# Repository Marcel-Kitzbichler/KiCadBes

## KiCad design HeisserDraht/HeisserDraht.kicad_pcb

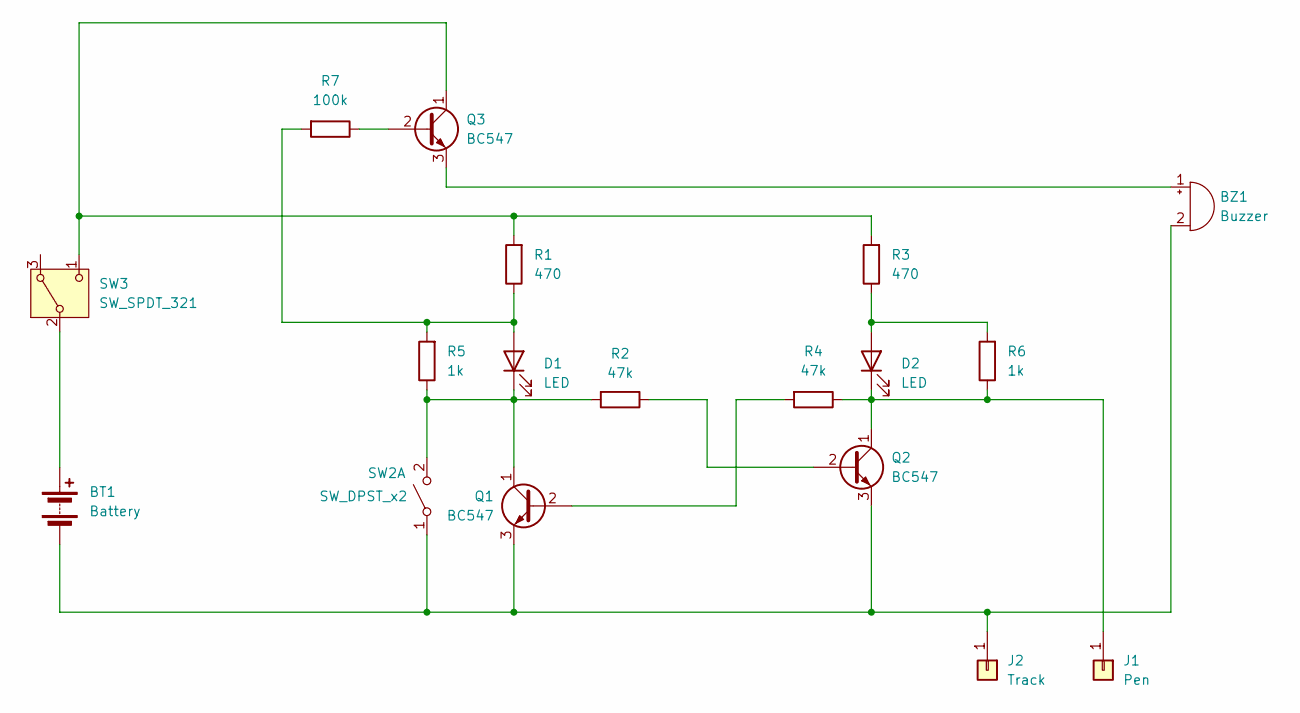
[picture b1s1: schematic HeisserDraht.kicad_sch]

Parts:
BT1: Battery; SolderWire-0.127sqmm_1x02_P3.7mm_D0.48mm_OD1mm_Relief2x
BZ1: Buzzer; BuzzerP_15,24
D1, D2: LED; LED_D5.0mm
J1: Pen; SolderWire-0.5sqmm_1x01_D0.9mm_OD2.3mm_Relief
J2: Track; SolderWire-1.5sqmm_1x01_D1.7mm_OD3.9mm
Q1, Q2, Q3: BC547; TO-92_Inline_Wide
R1, R3: 470; R_Axial_DIN0207_L6.3mm_D2.5mm_P10.16mm_Horizontal
R2, R4: 47k; R_Axial_DIN0207_L6.3mm_D2.5mm_P10.16mm_Horizontal
R5, R6: 1k; R_Axial_DIN0207_L6.3mm_D2.5mm_P10.16mm_Horizontal
R7: 100k; R_Axial_DIN0207_L6.3mm_D2.5mm_P10.16mm_Horizontal
SW2: SW_DPST_x2; SW_PUSH_6mm
SW3: SW_SPDT_321; SW_Slide-03_Wuerth-WS-SLTV_10x2.5x6.4_P2.54mm

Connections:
unnamed: BT1.1 (+), SW3.2 (B)
unnamed: BT1.2 (-), BZ1.2 (-), J2.1, Q1.3 (E), Q2.3 (E), SW2.1 (A)
unnamed: BZ1.1 (+), Q3.3 (E)
unnamed: D1.2 (A), R1.1, R5.2, R7.2
unnamed: D1.1 (K), Q1.1 (C), R2.2, R5.1, SW2.2 (B)
unnamed: D2.2 (A), R3.1, R6.2
unnamed: D2.1 (K), J1.1, Q2.1 (C), R4.1, R6.1
unnamed: Q1.2 (B), R4.2
unnamed: Q2.2 (B), R2.1
unnamed: Q3.2 (B), R7.1
unnamed: Q3.1 (C), R1.2, R3.2, SW3.1 (C)

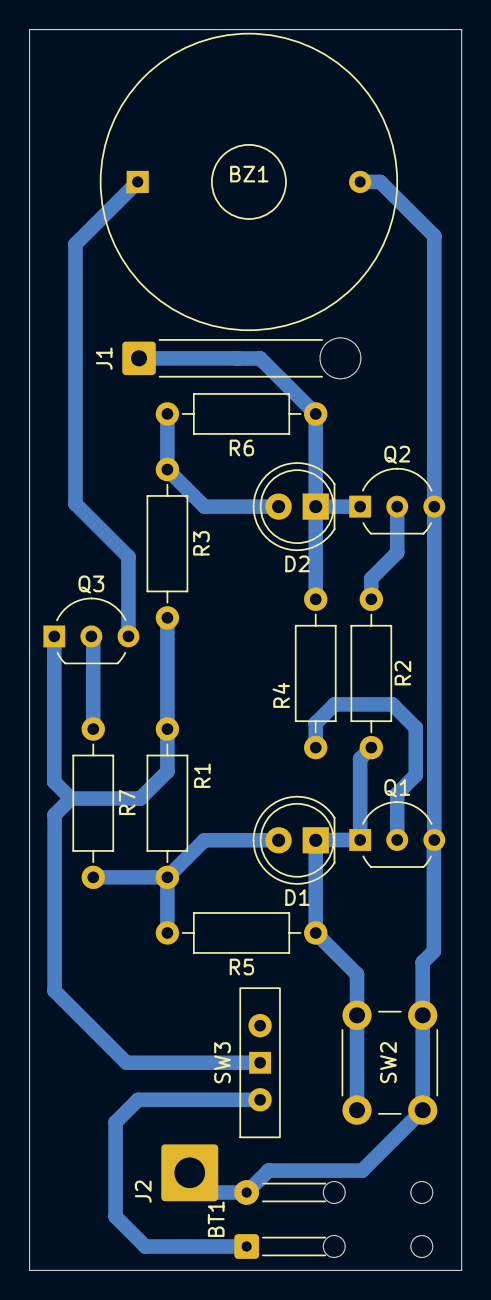
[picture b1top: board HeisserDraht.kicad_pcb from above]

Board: 2 copper layers, 29.6 x 85.0 mm, 18 parts (0 on the bottom side), 11 nets.

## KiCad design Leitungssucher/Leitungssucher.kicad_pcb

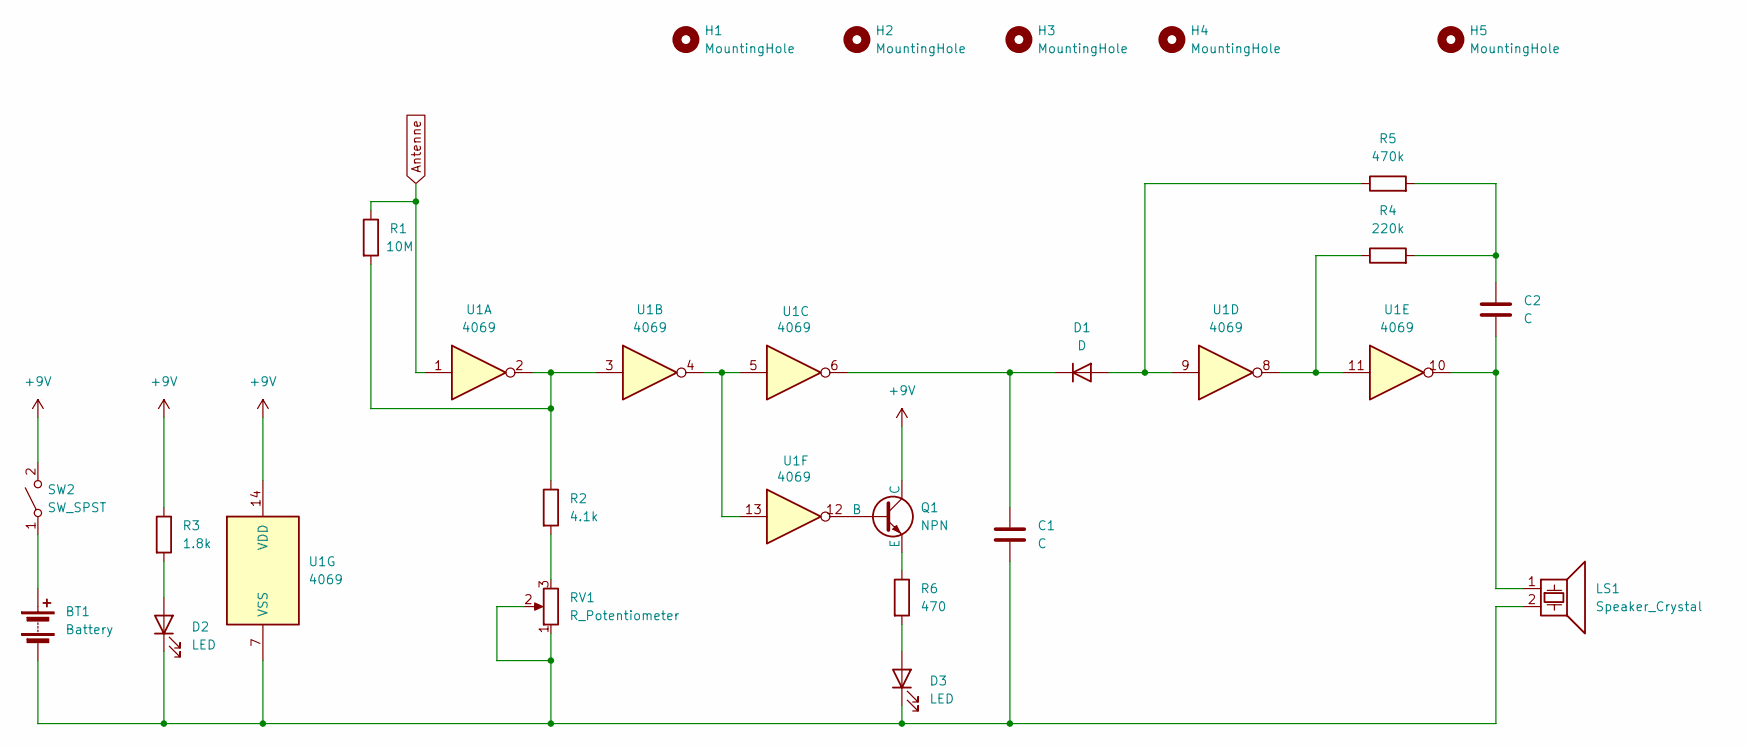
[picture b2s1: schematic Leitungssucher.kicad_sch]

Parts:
BT1: Battery; SolderWire-0.25sqmm_1x02_P4.2mm_D0.65mm_OD1.7mm
C1: C; C_Disc_D3.0mm_W2.0mm_P2.50mm
C2: C; C_Disc_D4.7mm_W2.5mm_P5.00mm
D1: D; D_DO-34_SOD68_P7.62mm_Horizontal
D2, D3: LED; SolderWire-0.25sqmm_1x02_P4.2mm_D0.65mm_OD1.7mm
H1, H2, H3, H4: MountingHole; MountingHole_3.7mm
H5: MountingHole; MountingHole_6mm
LS1: Speaker_Crystal; SolderWire-0.25sqmm_1x02_P4.2mm_D0.65mm_OD1.7mm
Q1: NPN; TO-92L_Inline_Wide
R1: 10M; R_Axial_DIN0207_L6.3mm_D2.5mm_P2.54mm_Vertical
R2: 4.1k; R_Axial_DIN0207_L6.3mm_D2.5mm_P10.16mm_Horizontal
R3: 1.8k; R_Axial_DIN0207_L6.3mm_D2.5mm_P10.16mm_Horizontal
R4: 220k; R_Axial_DIN0207_L6.3mm_D2.5mm_P10.16mm_Horizontal
R5: 470k; R_Axial_DIN0207_L6.3mm_D2.5mm_P10.16mm_Horizontal
R6: 470; R_Axial_DIN0207_L6.3mm_D2.5mm_P10.16mm_Horizontal
RV1: R_Potentiometer; Potentiometer_Piher_PT-10-V10_Vertical_Hole
SW2: SW_SPST; SolderWire-0.25sqmm_1x02_P4.2mm_D0.65mm_OD1.7mm
U1: 4069; DIP-14_W7.62mm_Socket

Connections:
+9V: Q1.1 (C), R3.1, SW2.2 (B), U1.14 (VDD)
Antenne: R1.1, U1.1
unnamed: BT1.1 (+), SW2.1 (A)
unnamed: BT1.2 (-), C1.2, D2.1 (K), D3.1 (K), LS1.2, RV1.1, RV1.2, U1.7 (VSS)
unnamed: C2.1, LS1.1, U1.10
unnamed: C2.2, R4.2, R5.2
unnamed: D1.2 (A), R5.1, U1.9
unnamed: C1.1, D1.1 (K), U1.6
unnamed: D2.2 (A), R3.2
unnamed: D3.2 (A), R6.2
unnamed: Q1.2 (B), U1.12
unnamed: Q1.3 (E), R6.1
unnamed: R1.2, R2.1, U1.2, U1.3
unnamed: R2.2, RV1.3
unnamed: R4.1, U1.8, U1.11
unnamed: U1.4, U1.5, U1.13

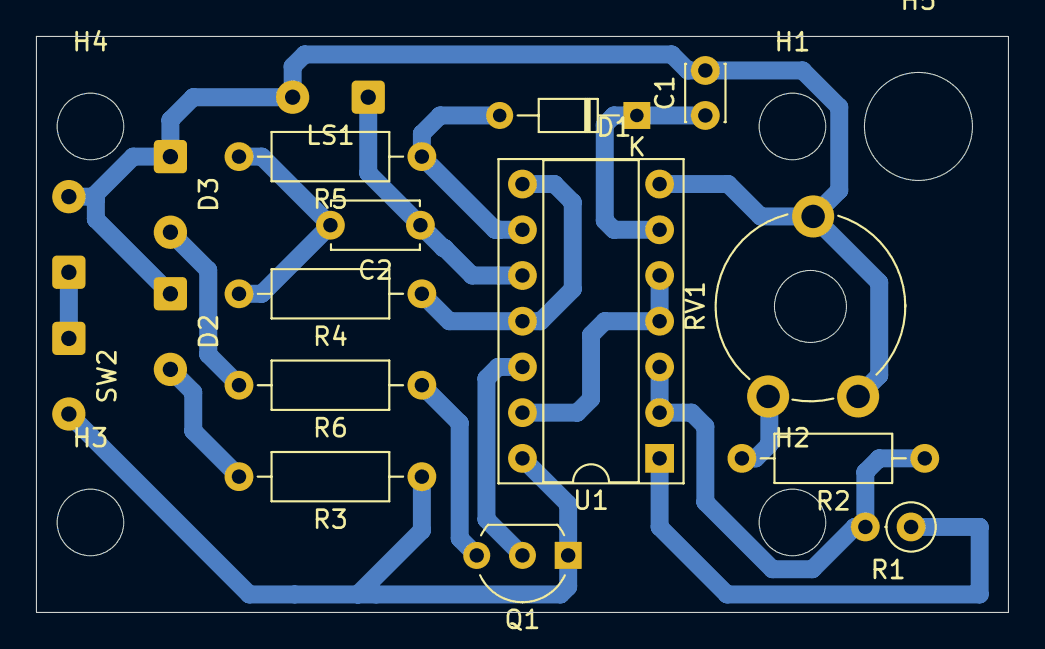
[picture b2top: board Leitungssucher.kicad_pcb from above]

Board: 2 copper layers, 54.0 x 32.0 mm, 22 parts (0 on the bottom side), 16 nets.

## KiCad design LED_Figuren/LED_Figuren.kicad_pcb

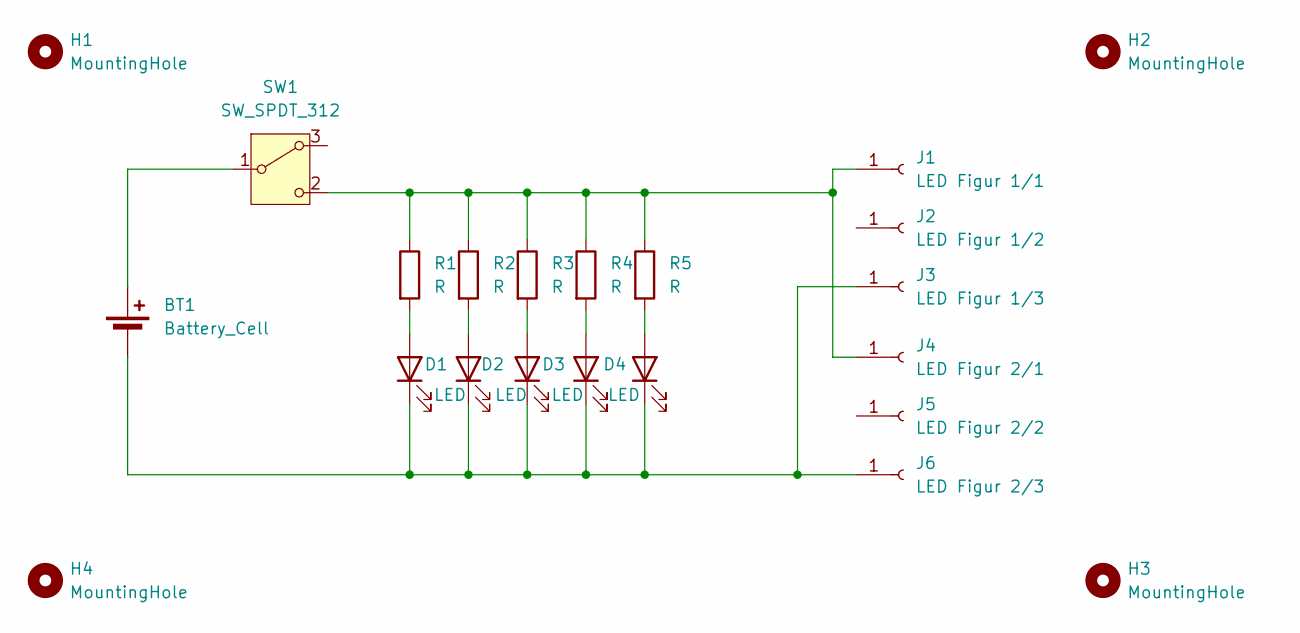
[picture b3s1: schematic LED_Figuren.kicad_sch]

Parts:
BT1: Battery_Cell; Varta CR2032
D1, D2, D3, D4, D5: LED; LED_D5.0mm
H1, H2, H3, H4: MountingHole; MountingHole_2.1mm
J1: LED Figur 1/1; PinHeader_1x01_P2.54mm_Vertical
J2: LED Figur 1/2; PinHeader_1x01_P2.54mm_Vertical
J3: LED Figur 1/3; PinHeader_1x01_P2.54mm_Vertical
J4: LED Figur 2/1; PinHeader_1x01_P2.54mm_Vertical
J5: LED Figur 2/2; PinHeader_1x01_P2.54mm_Vertical
J6: LED Figur 2/3; PinHeader_1x01_P2.54mm_Vertical
R1, R2, R3, R4, R5: R; R_Axial_DIN0207_L6.3mm_D2.5mm_P10.16mm_Horizontal
SW1: SW_SPDT_312; SW_Slide-03_Wuerth-WS-SLTV_10x2.5x6.4_P2.54mm

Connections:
unnamed: BT1.1 (+), SW1.1 (B)
unnamed: BT1.2 (-), D1.1 (K), D2.1 (K), D3.1 (K), D4.1 (K), D5.1 (K), J3.1, J6.1
unnamed: D1.2 (A), R1.2
unnamed: D2.2 (A), R2.2
unnamed: D3.2 (A), R3.2
unnamed: D4.2 (A), R4.2
unnamed: D5.2 (A), R5.2
unnamed: J1.1, J4.1, R1.1, R2.1, R3.1, R4.1, R5.1, SW1.2 (C)

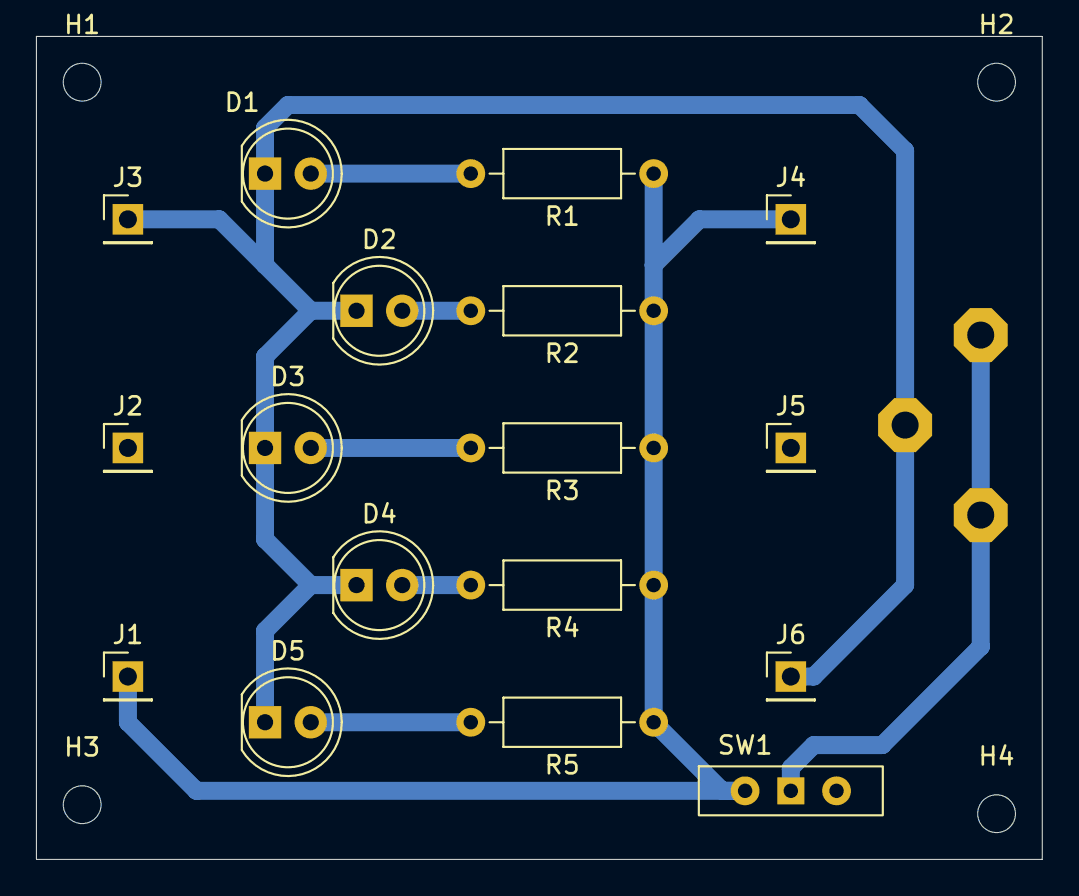
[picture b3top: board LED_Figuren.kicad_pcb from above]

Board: 2 copper layers, 55.9 x 45.7 mm, 22 parts (0 on the bottom side), 8 nets.

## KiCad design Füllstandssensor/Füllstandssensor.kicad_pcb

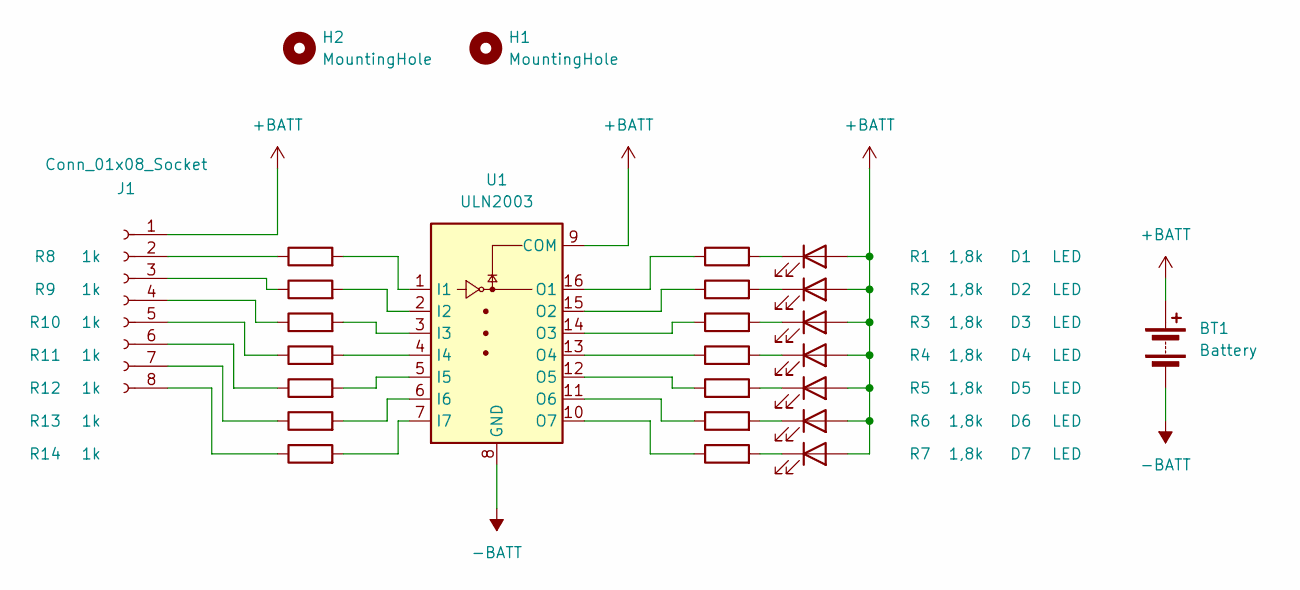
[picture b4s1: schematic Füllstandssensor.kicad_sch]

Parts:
BT1: Battery; PinHeader_1x02_P2.54mm_Vertical
D1, D2, D3, D4, D5, D6, D7: LED; LED_D3.0mm
H1, H2: MountingHole; MountingHole_3.5mm
J1: Conn_01x08_Socket; PinHeader_1x08_P2.54mm_Vertical
R1, R2, R3, R4, R5, R6, R7: 1,8k; R_Axial_DIN0207_L6.3mm_D2.5mm_P10.16mm_Horizontal
R8, R9, R10, R11, R12, R13, R14: 1k; R_Axial_DIN0207_L6.3mm_D2.5mm_P10.16mm_Horizontal
U1: ULN2003; DIP-16_W7.62mm_Socket

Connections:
+BATT: BT1.1 (+), D1.2 (A), D2.2 (A), D3.2 (A), D4.2 (A), D5.2 (A), D6.2 (A), D7.2 (A), J1.1, U1.9 (COM)
-BATT: BT1.2 (-), U1.8 (GND)
unnamed: D1.1 (K), R1.2
unnamed: D2.1 (K), R2.2
unnamed: D3.1 (K), R3.2
unnamed: D4.1 (K), R4.2
unnamed: D5.1 (K), R5.2
unnamed: D6.1 (K), R6.2
unnamed: D7.1 (K), R7.2
unnamed: J1.2, R8.1
unnamed: J1.3, R9.1
unnamed: J1.4, R10.1
unnamed: J1.5, R11.1
unnamed: J1.6, R12.1
unnamed: J1.7, R13.1
unnamed: J1.8, R14.1
unnamed: R8.2, U1.1 (I1)
unnamed: R9.2, U1.2 (I2)
unnamed: R10.2, U1.3 (I3)
unnamed: R11.2, U1.4 (I4)
unnamed: R12.2, U1.5 (I5)
unnamed: R13.2, U1.6 (I6)
unnamed: R14.2, U1.7 (I7)
unnamed: R1.1, U1.16 (O1)
unnamed: R2.1, U1.15 (O2)
unnamed: R3.1, U1.14 (O3)
unnamed: R4.1, U1.13 (O4)
unnamed: R5.1, U1.12 (O5)
unnamed: R6.1, U1.11 (O6)
unnamed: R7.1, U1.10 (O7)

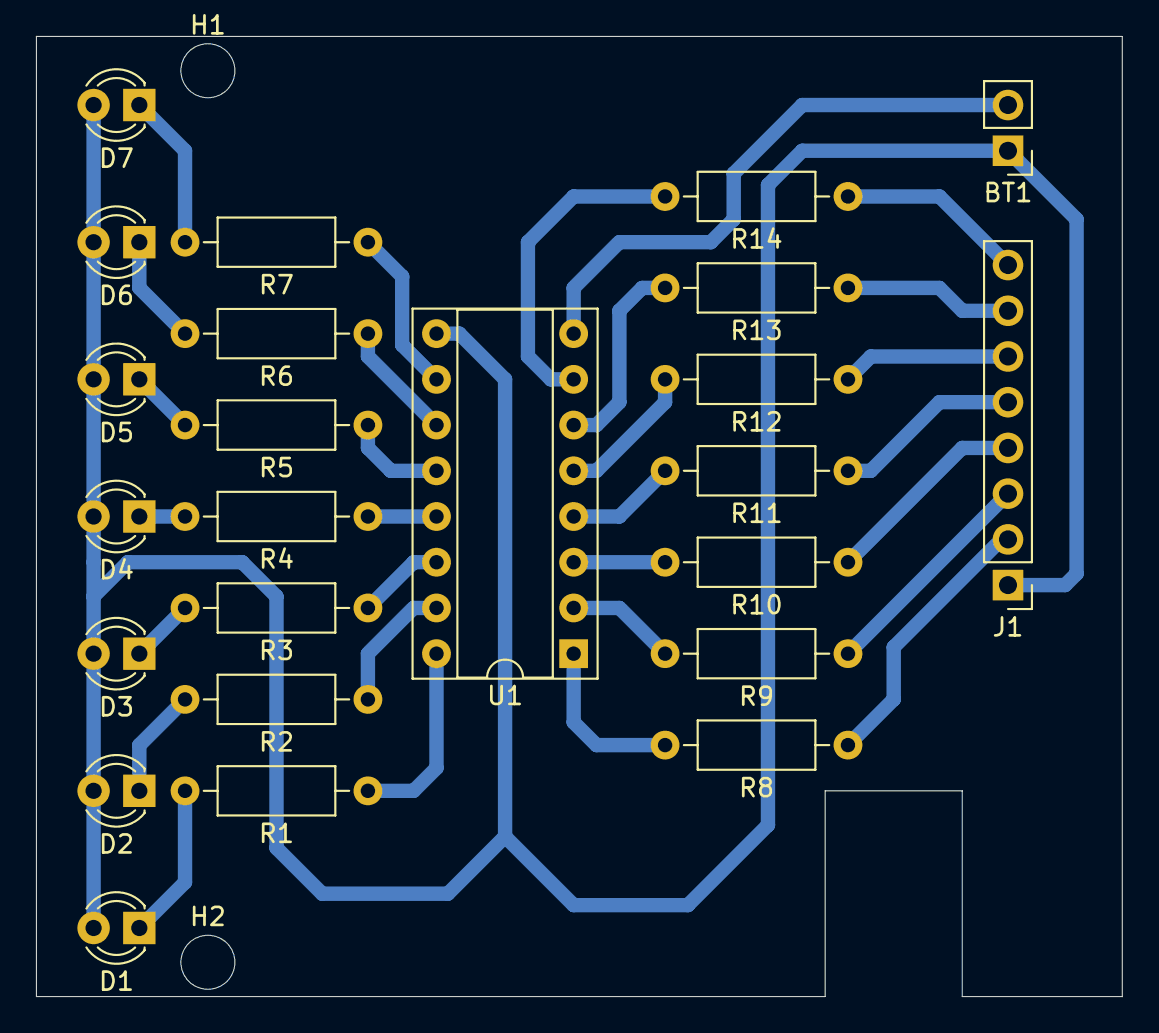
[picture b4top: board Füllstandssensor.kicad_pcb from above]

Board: 2 copper layers, 60.3 x 53.3 mm, 26 parts (0 on the bottom side), 30 nets.

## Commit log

2025-01-21 init
2025-02-05 heisser draht v1
2025-02-05 added resistor values
2025-02-05 updated resistore values
